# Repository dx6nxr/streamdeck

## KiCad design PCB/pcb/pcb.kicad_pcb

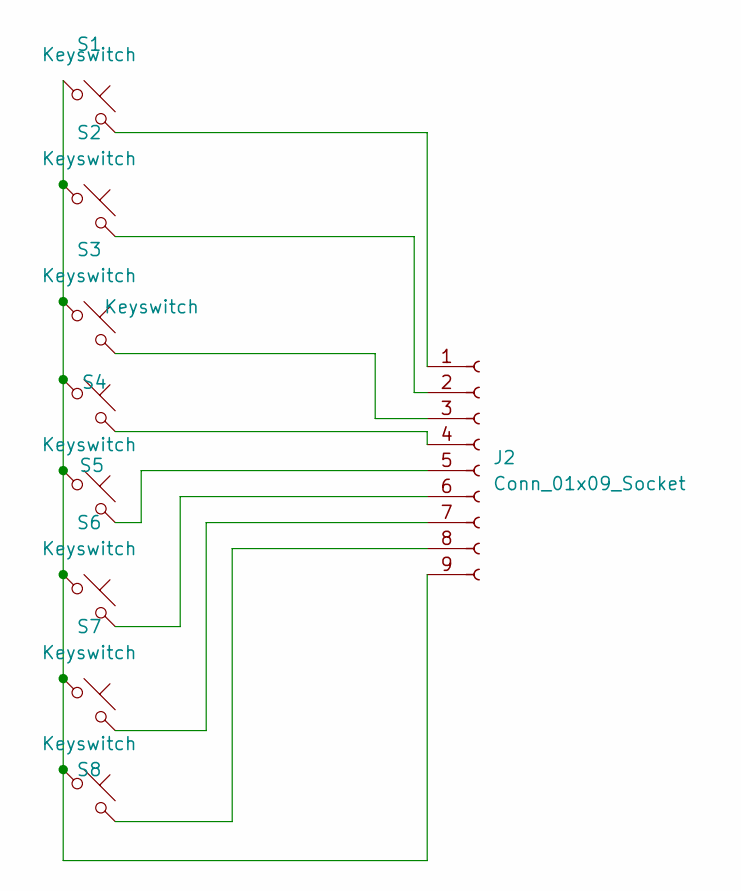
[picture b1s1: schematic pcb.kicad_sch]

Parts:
J2: Conn_01x09_Socket; PinSocket_1x09_P1.27mm_Vertical
S1, S2, S3, S4, S5, S6, S7, S8: Keyswitch; SW_Hotswap_Kailh_MX_1.00u

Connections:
unnamed: J2.1, S1.2
unnamed: J2.2, S2.2
unnamed: J2.3, S3.2
unnamed: J2.4, S4.2
unnamed: J2.5, S5.2
unnamed: J2.6, S6.2
unnamed: J2.7, S7.2
unnamed: J2.8, S8.2
unnamed: J2.9, S1.1, S2.1, S3.1, S4.1, S5.1, S6.1, S7.1, S8.1

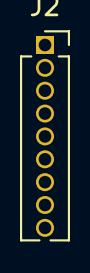
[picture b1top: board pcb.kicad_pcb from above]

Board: 2 copper layers, 9 parts (0 on the bottom side), 9 nets.

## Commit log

2025-01-07 Add .gitattributes, .gitignore, README.md, and LICENSE.txt.
2025-01-07 Add project files.
2025-01-11 changelog: - Buffer reading is now more realiable and sleep is removed - additional thread is being spawned for the com reading and slider/key function application - added the COM port scan and choic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
2025-01-20 - Added auto reconnection on disconnect. - new UI based on wt is in work.
2025-01-23 Create LICENSE
2025-01-25 new qt ui
2025-02-23 Added support for key sequences
    Added support for binding key sequences to the buttons (i.e. ctrl+v).
2025-03-20 v.1.0.0 body files released
    - fusion 360 project
    - stl for body
    - stl for bottom cover
2025-03-27 New case + bug fix
    - Uploaded new case files for printing
    - fixed a bug where the com port wont be saved into a config
2025-03-28 New updated case
2025-04-13 New app in development (wasapi)
2025-04-14 UI v1
2025-04-14 It woooorks!!!!
2025-04-15 Added Material you theme
2025-04-15 Theme adjustments
2025-04-15 some more UI tweaks
2025-04-17 testing next.js + shadcn UI
2025-11-23 kinda update ig
2025-11-24 apps now should be refreshed when the volume of any group is changed
2026-01-04 Cleanup
    - removed old case model
    - removed old app code
